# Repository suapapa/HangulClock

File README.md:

# 한글시계 - HangulClock

한글시계는 오픈소스(SW/HW) 입니다. [시연 동영상](https://youtu.be/ApymC7qAVTI)

- Make Korea의 2011 컨테스트 수상 작 (1등 없는 2등)
- [A Word Clock by drj113](http://www.instructables.com/id/A-Word-Clock/)에서 영감을 얻었습니다.

## 소스코드

### Rusty HangulClock

~~Please Refer [rusty_hangulclock/README.md](rusty_hangulclock/README.md)~~

> ⚠️ Moved to seperated repository [suapapa/rusty-hangulclock](https://github.com/suapapa/rusty-hangulclock)

### Go program which using Periph.io

Build for ARM64 SBCs:

    $ cd go_hangulclock
    $ GOARCH=arm64 GOOS=linux go build

Then, install binary and system service config by reference `deploy.sh`

### Arduino Sketch (prototype)

Need update submoduls HT1380 and LedControl to build the sketch;

    $ git submodule update

## 링크

- 블로그 글:
  - [다시만든 한글시계 with 러스트](https://homin.dev/blog/post/20241222_rusty_hangulclock/) - 2024-12
  - [11년 만에 완성한, 원조, 한글시계](https://homin.dev/blog/post/20221009_hangulclock_is_re-written_in_golang/) - 2022-09
  - [한글시계 뒷 이야기](https://homin.dev/blog/p=493/) - 2011-11

## 라이선스

### 5x5 한글 조합 - BY-CC

<br />이 저작물은 <a rel="license" href="http://creativecommons.org/licenses/by/4.0/">크리에이티브 커먼즈 저작자표시 4.0 국제 라이선스</a>에 따라 이용할 수 있습니다.

### 소스코드 - OpenSource

아두이노 스케치와, 고 프로그램의 라이선스가 각각 다릅니다. 각각의 폴더에서 확인하세요.
- Rust program: [rusty_hangulclock/LICENSE](rusty_hangulclock/LICENSE) - BSD
- Go program: [go_hangulclock/LICENSE](go_hangulclock/LICENSE) - BSD
- Arduino Sketch: [ardino/HangulClock/LICENSE](arduino/HangulClock/LICENSE) - GPL

### 회로도, 아트워크, 케이스 및 그 밖의 파일들 - Proprietary

회로도, 아트워크, 케이스 설계 파일 및 그 밖의 모든 파일들은 독점 라이선스 하에 있습니다. 
이러한 파일들의 사용, 복제, 수정, 배포는 저작권자의 명시적 허가 없이는 금지됩니다.

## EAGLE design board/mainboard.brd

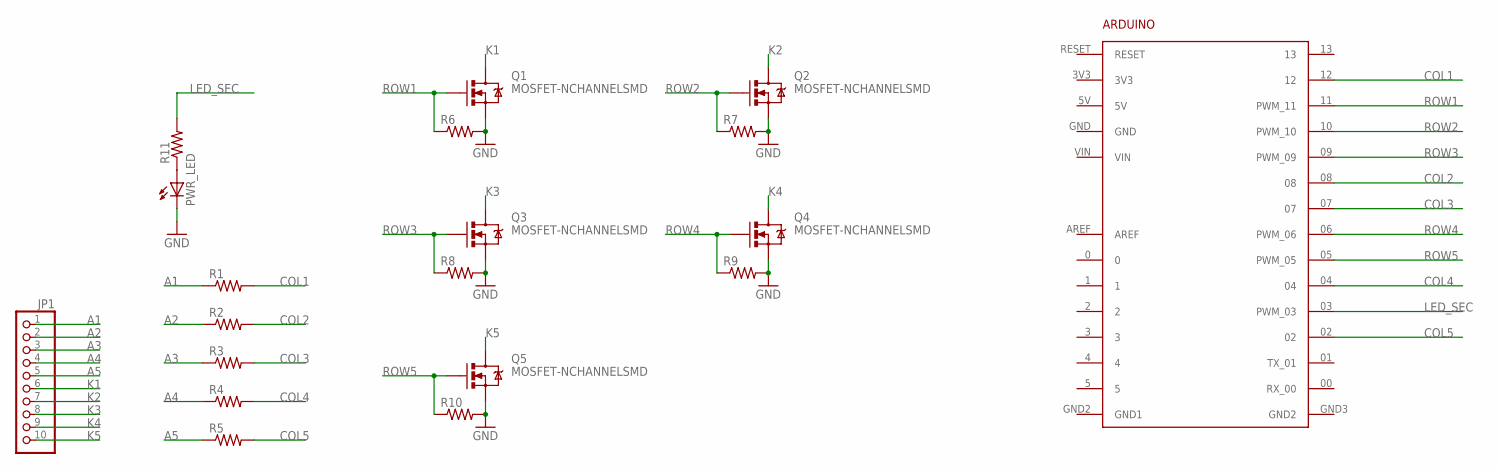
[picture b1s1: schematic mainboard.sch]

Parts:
ARDUINO1: ARDUINO
JP1: PINHD-1X10; 1X10
PWR_LED: LED5MM
Q1, Q2, Q3, Q4, Q5: MOSFET-NCHANNELSMD; SOT23-3
R1, R2, R3, R4, R5, R6, R7, R8, R9, R10, R11: R-US_M1206; M1206

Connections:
3V3: ARDUINO1.3V3
5V: ARDUINO1.5V
A1: JP1.1, R1.1
A2: JP1.2, R2.1
A3: JP1.3, R3.1
A4: JP1.4, R4.1
A5: JP1.5, R5.1
COL1: ARDUINO1.12, R1.2
COL2: ARDUINO1.08, R2.2
COL3: ARDUINO1.07, R3.2
COL4: ARDUINO1.04, R4.2
COL5: ARDUINO1.02, R5.2
GND: ARDUINO1.GND, PWR_LED.K (C), Q1.2 (S), Q2.2 (S), Q3.2 (S), Q4.2 (S), Q5.2 (S), R6.2, R7.2, R8.2, R9.2, R10.2
GND1: ARDUINO1.GND2 (GND1)
GND2: ARDUINO1.GND3 (GND2)
K1: JP1.6, Q1.3 (D)
K2: JP1.7, Q2.3 (D)
K3: JP1.8, Q3.3 (D)
K4: JP1.9, Q4.3 (D)
K5: JP1.10, Q5.3 (D)
LED_SEC: ARDUINO1.03 (PWM_03), R11.2
unnamed: PWR_LED.A, R11.1
ROW1: ARDUINO1.11 (PWM_11), Q1.1 (G), R6.1
ROW2: ARDUINO1.10 (PWM_10), Q2.1 (G), R7.1
ROW3: ARDUINO1.09 (PWM_09), Q3.1 (G), R8.1
ROW4: ARDUINO1.06 (PWM_06), Q4.1 (G), R9.1
ROW5: ARDUINO1.05 (PWM_05), Q5.1 (G), R10.1
VIN: ARDUINO1.VIN

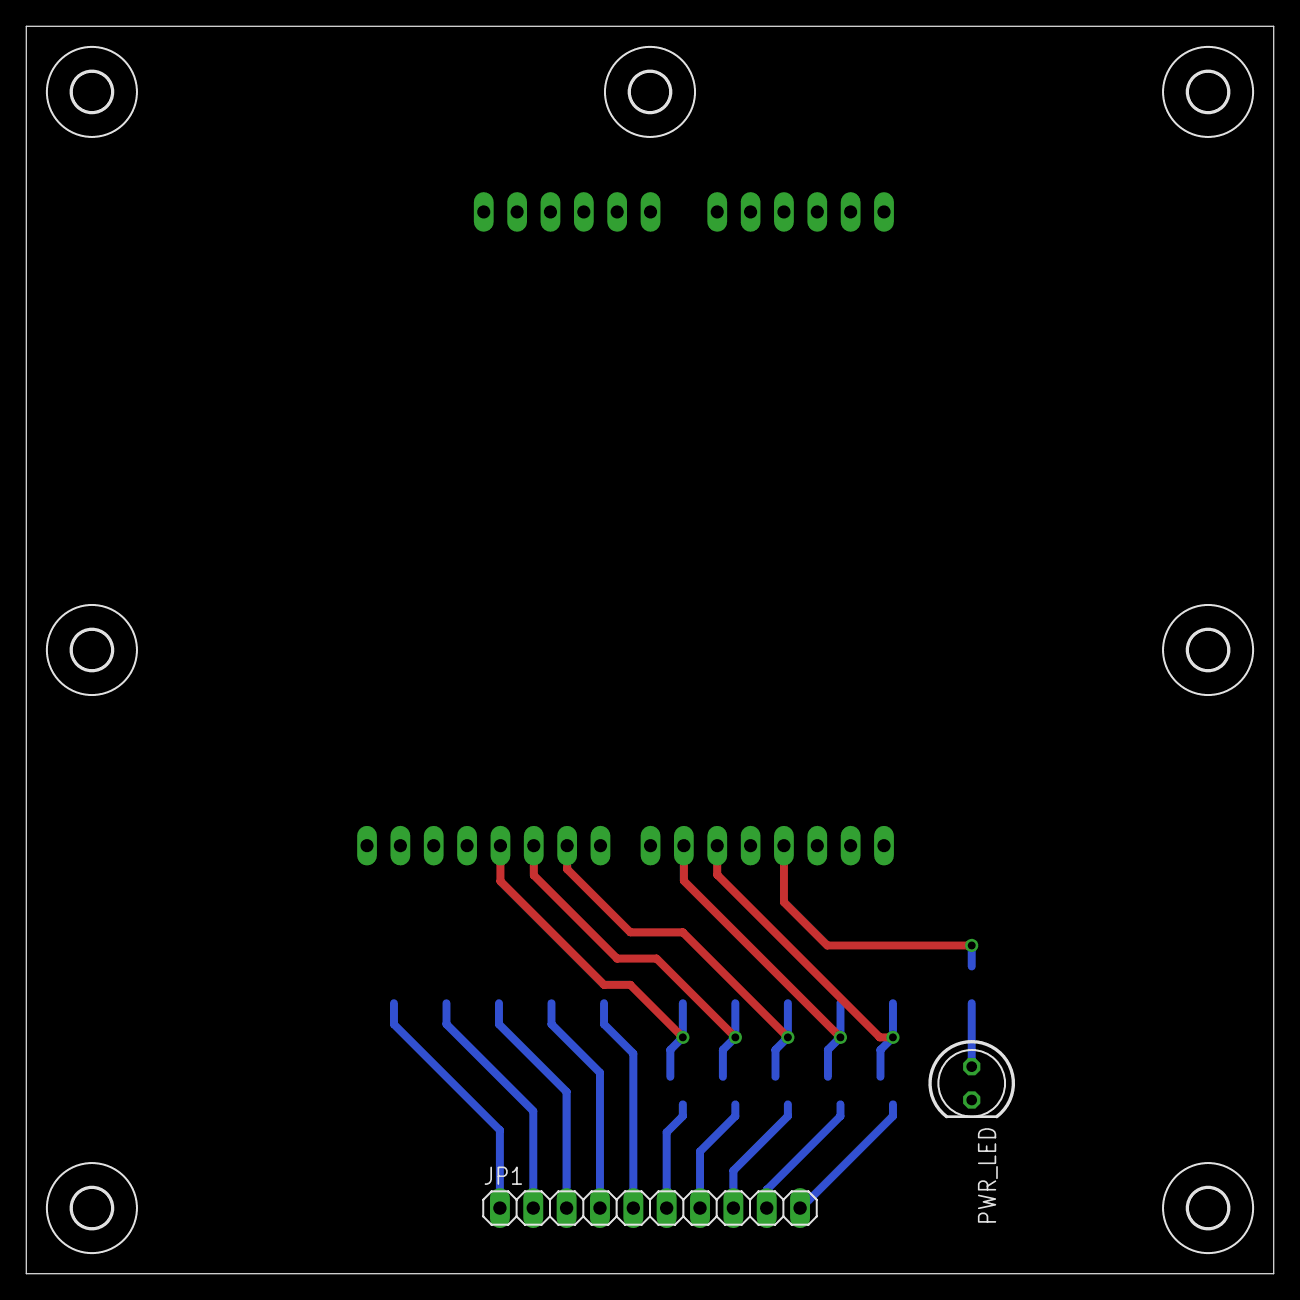
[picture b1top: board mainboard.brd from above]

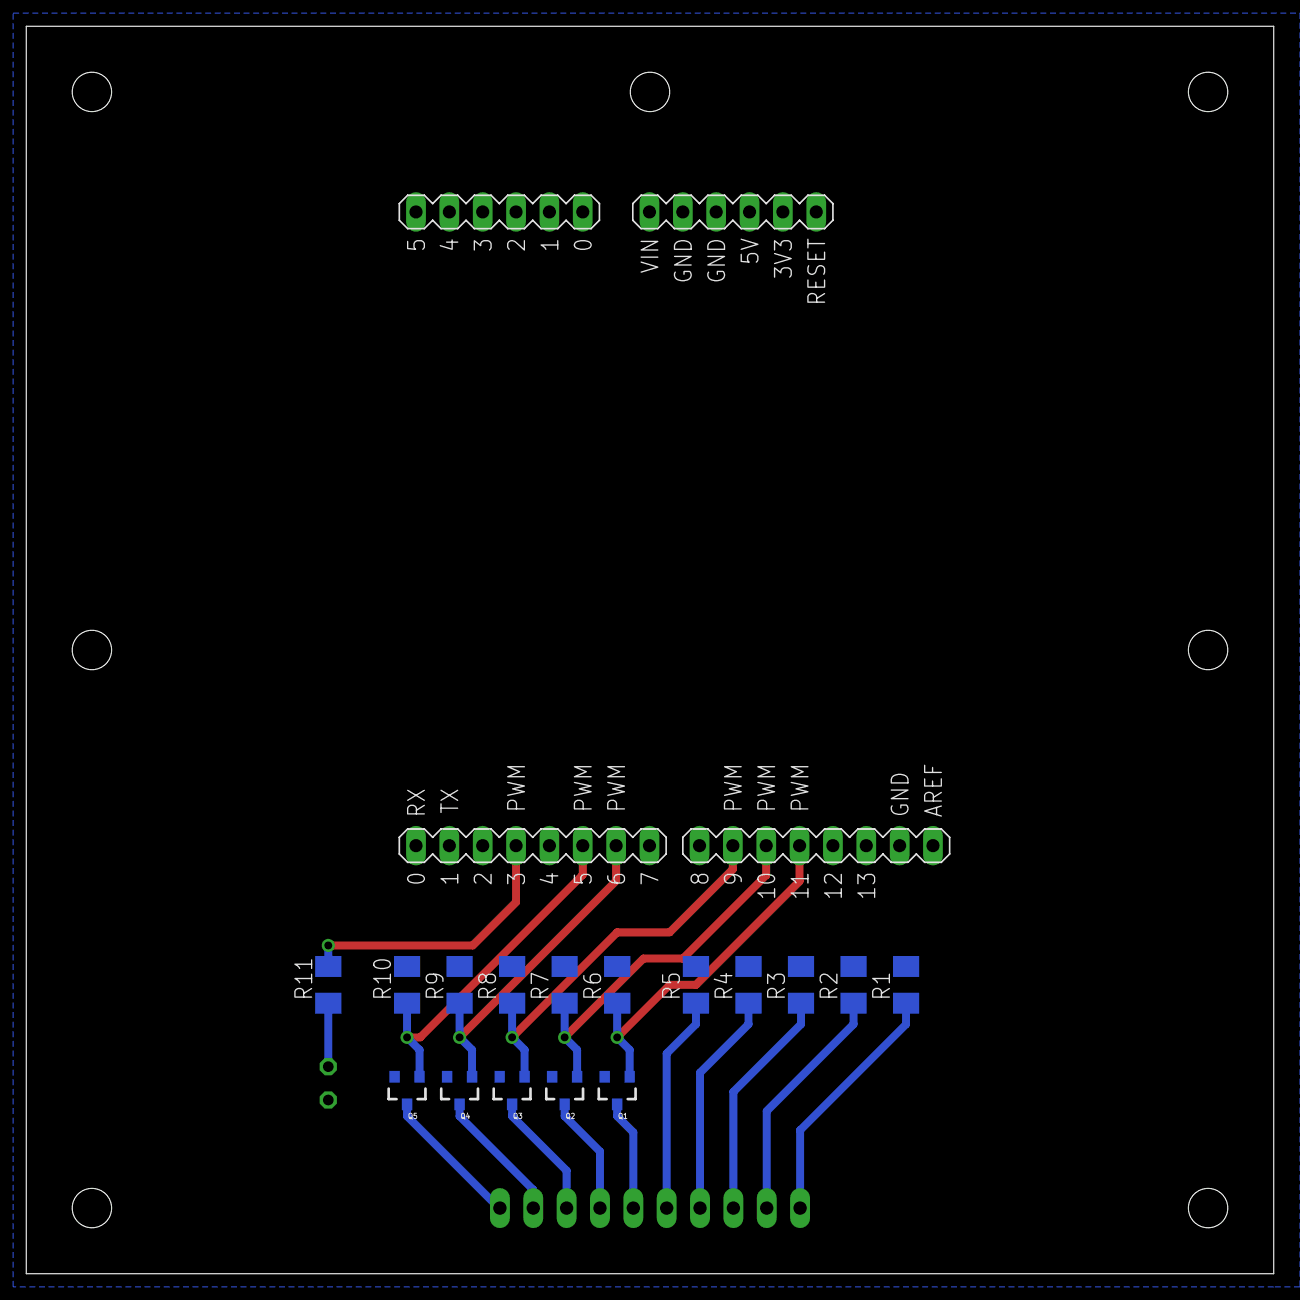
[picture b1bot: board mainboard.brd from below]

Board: 2 copper layers, 95.0 x 95.0 mm, 26 parts (17 on the bottom side), 23 nets.

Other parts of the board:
U$1, U$2, U$3, U$4, U$5, U$6, U$7: 3,0

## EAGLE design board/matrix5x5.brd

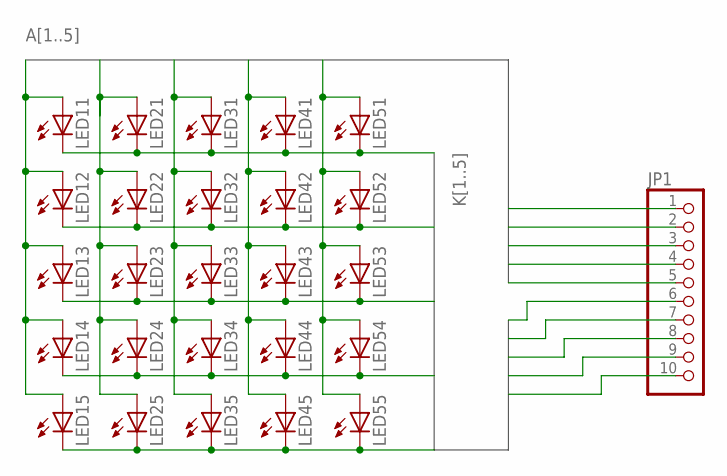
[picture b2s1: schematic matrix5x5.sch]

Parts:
JP1: PINHD-1X10; 1X10
LED11, LED12, LED13, LED14, LED15, LED21, LED22, LED23, LED24, LED25, LED31, LED32, LED33, LED34, LED35, LED41, LED42, LED43, LED44, LED45, LED51, LED52, LED53, LED54, LED55: LED5MM

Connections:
A1: JP1.1, LED11.A, LED12.A, LED13.A, LED14.A, LED15.A
A2: JP1.2, LED21.A, LED22.A, LED23.A, LED24.A, LED25.A
A3: JP1.3, LED31.A, LED32.A, LED33.A, LED34.A, LED35.A
A4: JP1.4, LED41.A, LED42.A, LED43.A, LED44.A, LED45.A
A5: JP1.5, LED51.A, LED52.A, LED53.A, LED54.A, LED55.A
K1: JP1.6, LED11.K (C), LED21.K (C), LED31.K (C), LED41.K (C), LED51.K (C)
K2: JP1.7, LED12.K (C), LED22.K (C), LED32.K (C), LED42.K (C), LED52.K (C)
K3: JP1.8, LED13.K (C), LED23.K (C), LED33.K (C), LED43.K (C), LED53.K (C)
K4: JP1.9, LED14.K (C), LED24.K (C), LED34.K (C), LED44.K (C), LED54.K (C)
K5: JP1.10, LED15.K (C), LED25.K (C), LED35.K (C), LED45.K (C), LED55.K (C)

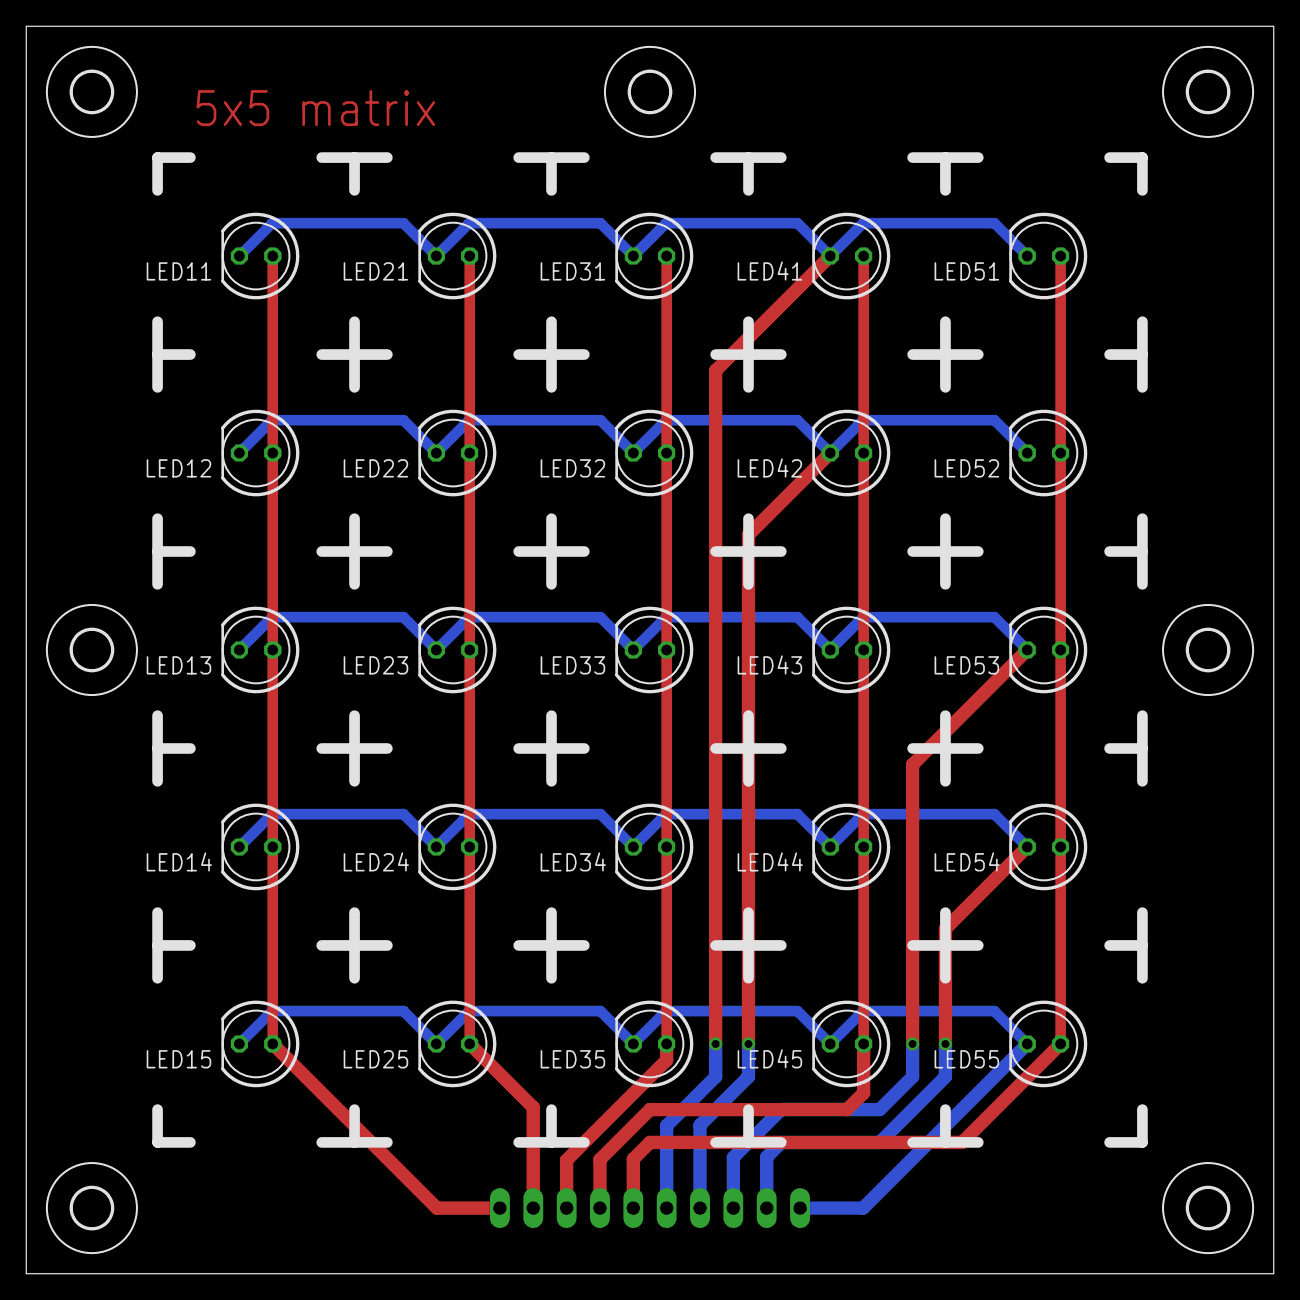
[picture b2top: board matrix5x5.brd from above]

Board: 2 copper layers, 95.0 x 95.0 mm, 33 parts (1 on the bottom side), 10 nets.

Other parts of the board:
U$1, U$2, U$3, U$4, U$5, U$6, U$7: 3,0

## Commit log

2011-03-29 Added README.md
2011-03-29 arduino: added skel sketch from arscons, http://code.google.com/p/arscons/
2011-03-29 arduino: added code for basic test for matrix
2011-03-30 arduino: replaced more good looking mat test.
2011-05-17 tools: script for making silkscreen of panel
2011-05-17 tool: make_panel.py: set dpi info to final image
2011-05-17 tool: make_panel.py: set fontSize at run time
2011-05-19 make_panel.py: mirroring for toner-transfer
2011-06-10 arduino: added brightness control
2011-06-14 arduino: added codes for turn on leds for given H and M
2011-06-14 arduino: added library for RTC, HT1380
2011-06-14 arduino: added func for set RTC
2011-06-14 arduino: Added serial command for funcs of the clock
2011-06-26 arduino: Rotated matrix, more test with serial command
2011-06-28 arduino: round up minute in step 5
2011-06-28 board: added eaglecad schs
2011-06-29 arduino: cleaned code
2011-06-29 arduino: removed rtc codes
2011-06-30 arduino: fixed bug on show_time()
2011-07-20 arduino: fixed to update current time in every sec
2011-07-20 arduino: added RTC, HT1380
2011-07-27 arduino: fixed to using ATmega8L, 8MHz
    you should add new board to;
    /usr/share/arduino/hardware/arduino/boards.txt
    add new board atmega8l like this;
    atmega8l.name=Arduino8L 8MHz
    atmega8l.upload.protocol=arduino
    atmega8l.upload.maximum_size=7168
2011-10-09 README.md: update documents
2012-06-01 Porting to Arduino 1.0.x
2012-06-01 libs in submodule
2012-06-01 arduino fixed sketch works with Arduino 1.x
2012-06-01 Added .gitignore
2012-06-01 update the clock in every 5 secs
    1min seems too long. no update happened.
2012-06-01 added tick-tock blink
2012-06-03 README.md: add guide to update submodules
2012-06-05 Fixes in MakerFair Korea 2012
2012-06-07 add -symbolic linked- HangulClock.pde
2013-06-07 README.md: Add image and license
2013-06-07 README.md: clean up
2013-07-29 board: add artwork for sketch
2013-08-02 board: fix net name and add artwork
2013-08-02 Add Korean README
2013-08-03 board: add more holes to matrix board
2013-08-04 board: adding main board
2013-08-05 board: add more components into mainboard
2013-08-06 board: add arduino to mainboard
2013-08-11 tools/make_panel.py: fix hard-coded values
    * Add panel margin
    * Reduce one char-box from 20x20 to 15x15 (mm)
2014-07-16 fix submodule address
2014-07-16 Add submodule for ds1302
2014-07-16 change rtc to ds1302
2014-07-16 remove submodule HT1380
2015-10-08 Update Daddy's LAB's code
    Code came from following links:
    * HangulClock.ino: https://github.com/byoungcheolyi/Arduino
    * libs/RTClib: http://cafe.naver.com/daddyslab/188
    * libs/Button: http://cafe.naver.com/daddyslab/189
2015-10-08 Add rhino 3d model files from Daddy's Lab
    Files came from following link:
    * http://cafe.naver.com/daddyslab/221
2015-10-10 Add news about onsale HangulClock
2015-10-11 Add link for Daddy's LAB
2017-04-15 add svg panel generator
2017-04-15 add base_guide
2017-04-15 Add sketch
2017-12-14 README.md: fix broken links
2018-01-12 README.md: remove broken market link
2018-12-13 README.md: 여러분들의 한글시계 사이트 등록
2020-10-20 update license
2022-10-08 add go version
2022-10-08 add system service file and deploy script
2022-10-09 update LICENSEs
2024-12-18 add rusty_hangulclock
2024-12-18 pix tool for python3
2024-12-18 add example font
2024-12-18 fix make_panel script
2024-12-19 fix font to 소요단풍체
2024-12-19 rust: add dotstar led strip
2024-12-19 add files for case
2024-12-21 fix case size
2024-12-21 rs: implement hangulclock
2024-12-21 case: add back
2024-12-21 rs: bugfix
2024-12-23 finetune case
2024-12-30 fix case back
2024-12-31 light panel
2025-01-01 add kicad sch and gerber
2025-01-01 sch: pcb round routes
2025-01-03 fix dimention
2025-01-04 fix sch and pcb
2025-01-14 rusty_hangulclock: change mcu to esp32c3
2025-01-15 split code to files
2025-01-15 rusty_hangulclock: use wps
2025-01-15 update menu
2025-01-15 fix wrong idx
2025-01-16 don't update panel while wifi in use
2025-01-26 wifi working...
2025-01-26 wps, ntp works
2025-01-26 ntp, wps works seperately
2025-01-26 use nvs to store wifi cred
2025-01-27 add .gitignore
2025-01-28 set wifi tx power for esp32c3-supermini
2025-01-30 select dotstart and neopixel with feature
2025-01-31 sch: re-draw sch and artwork for v1.0.0
2025-02-02 sch: fix pcb
2025-02-02 fix pcb
2025-02-03 update sch and gerber
2025-02-07 panel: select font and y_offset with cmdline arg.
2025-02-08 case: fix case to reduce print time
2025-02-12 case: update case
2025-02-14 rusty_hangulclock: add photos
2025-02-15 rusty_hangulclock: add rotary encoder test code
2025-02-15 rusty_hangulclock: set mutex to sled
2025-02-16 rusty-hangulclock: fix warnnings
2025-02-23 rm oled code
2025-05-11 rusty_hangulclock: update README.md for toolchain installation and flashing commands
2025-05-11 fix(rusty-hangulclock): fix burst input
2025-05-11 feat(rusty-hangulclock): implement rotary encoder event handling
2025-05-11 refactor(rusty-hangulclock): move rotary encoder logic to separate module
2025-05-12 refactor(rusty-hangulclock): improve menu interaction and rotary event handling
2025-05-12 feat(rusty-hangulclock): add RESULT_NET mutex for command result handling and update menu display
2025-05-12 feat(rusty-hangulclock): add CUR_H and CUR_M mutexes for current time tracking and update menu display with time
2025-05-12 refactor(rusty-hangulclock): enhance time display logic with improved NTP handling and menu state management
2025-05-12 feat(rusty-hangulclock): add LED color settings to menu and global state management
2025-05-12 feat(rusty-hangulclock): integrate HSV settings storage and retrieval with NVS for LED color management
2025-05-13 feat: remap_leds
2025-05-13 feat(rusty-hangulclock): update initialization message and add turn_on_all method for LED control
2025-05-15 feat: rev7.
2025-05-15 feat: add timezone menu
2025-05-15 docs: update README
2025-09-08 fix: fix broken image link
2025-09-08 feat: update LICENSE

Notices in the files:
README.md:
CC BY 4.0
